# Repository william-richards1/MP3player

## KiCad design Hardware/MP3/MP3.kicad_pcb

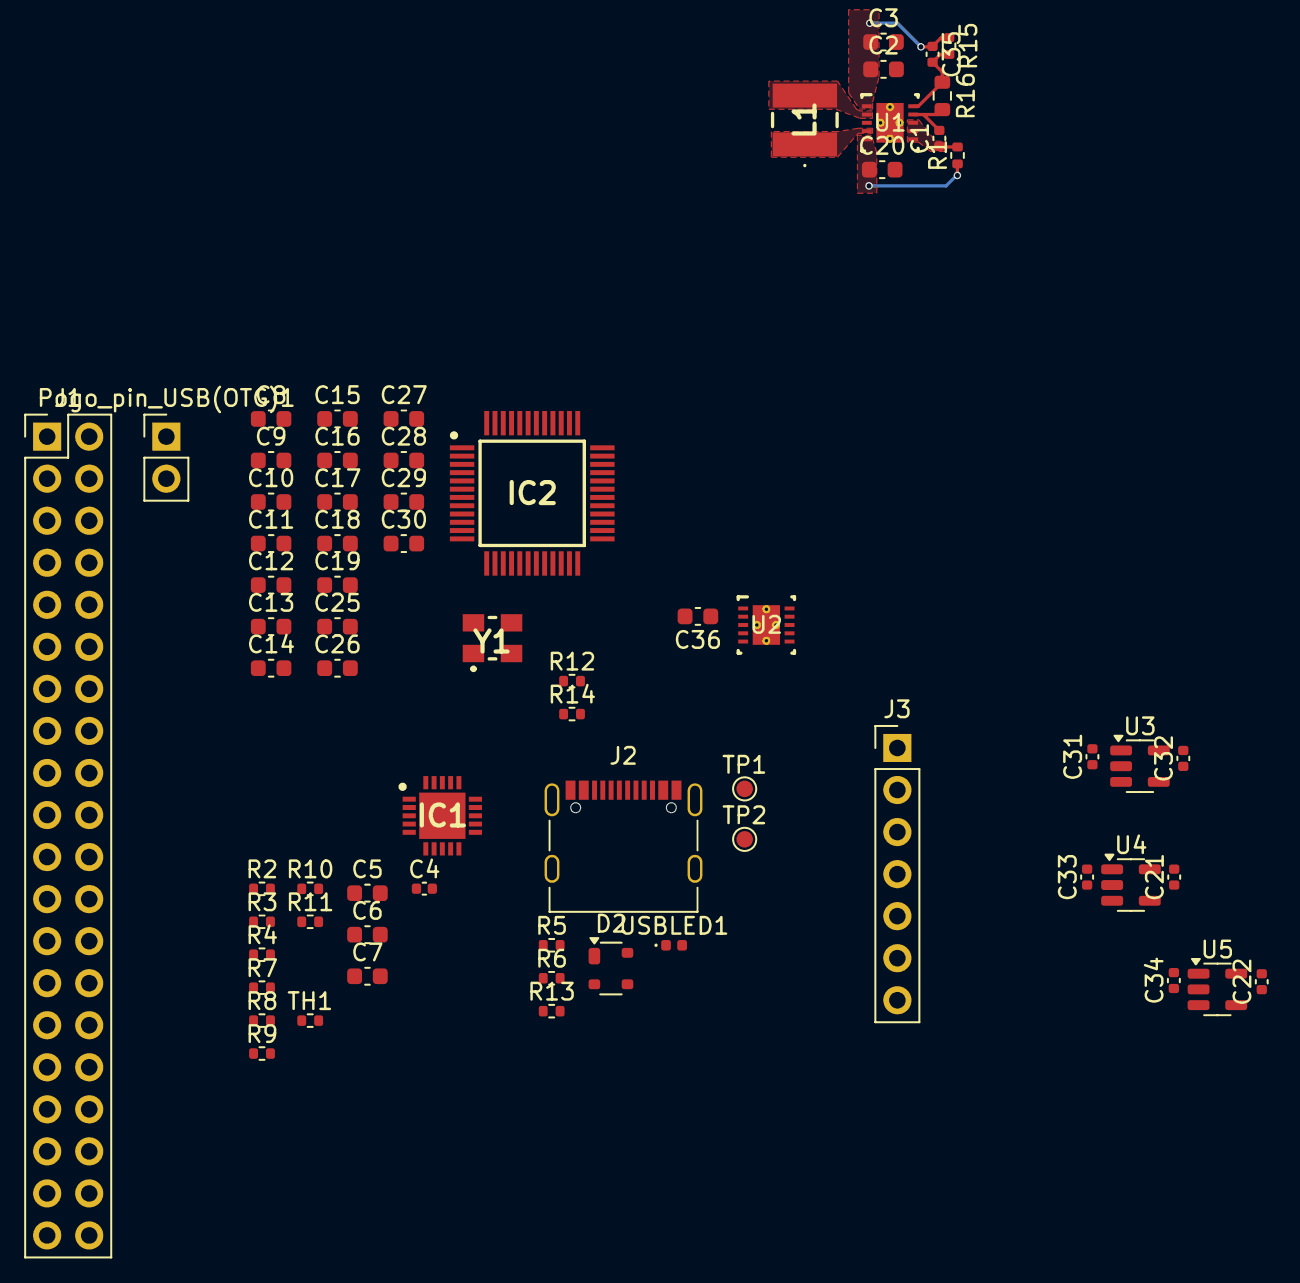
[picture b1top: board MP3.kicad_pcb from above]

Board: 4 copper layers, 68 parts (0 on the bottom side), 38 nets.

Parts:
C1, C4: 0.1uF; C_0402_1005Metric
C2: 22uF; C_0603_1608Metric
C3: 47uF; C_0603_1608Metric
C5, C9, C11, C13, C14, C17, C18, C20, C25, C28, C29, C36: 10uF; C_0603_1608Metric
C6, C7: 4.7uF; C_0603_1608Metric
C8, C10, C12, C15, C19, C26, C30: 0.1uF; C_0603_1608Metric
C16, C27: 470uF; C_0603_1608Metric
C21, C22, C31, C32, C33, C34: 1uF; C_0402_1005Metric
C35: 1nF; C_0402_1005Metric
D2: SP0503BAHT; SOT-143
IC1: MCP73871-2CCI_ML; QFN50P400X400X100-21N-D
IC2: AK4493SEQ; QFP50P900X900X160-48N
J1: Conn_02x20_Odd_Even; PinHeader_2x20_P2.54mm_Vertical
J2: USB_C_Receptacle_USB2.0; USB_C_Receptacle_Palconn_UTC16-G
J3: Conn_01x07_Pin; PinHeader_1x07_P2.54mm_Vertical
L1: LPS4012-223MRC; LPS4012223MRC
Pogo_pin_USB(OTG)1: Conn_01x02_Male; PinHeader_1x02_P2.54mm_Vertical
R1: 100; R_0402_1005Metric
R2: 2.49k; R_0402_1005Metric
R3: 24.9k; R_0402_1005Metric
R4: 2.0k; R_0402_1005Metric
R5, R6, R13: 5.1k; R_0402_1005Metric
R7, R8, R11: 10k; R_0402_1005Metric
R9: 330k; R_0402_1005Metric
R10: 100k; R_0402_1005Metric
R12, R14: 10; R_0402_1005Metric
R15: 1.96MΩ; R_0402_1005Metric
R16: 208kΩ; R_0603_1608Metric
TH1: Thermistor_NTC 10k; R_0402_1005Metric
TP1, TP2: TestPoint; TestPoint_Pad_D1.0mm
U1: TPS63000DRCR; DRC0010J
U2: OPA1622IDRCR; DRC0010J
U3, U5: TPS7A20xxxDBV; SOT-23-5
U4: TPS7A2033PDBVR; SOT-23-5
USBLED1: WHITE_LED; LED_0402_1005Metric
Y1: ABM8-22.5792MHZ-D2Y-T; ABM810000MHZ12D2W

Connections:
3V3: C8.2, C9.1, IC1.4 (PROG2), IC2.48 (TVDD), R7.1, R8.2, R11.1
+5.2V: C2.1, C3.1, C31.2, C33.2, C34.2, C35.1, R15.1, U1.1 (VOUT), U3.1 (IN), U4.1 (IN), U5.1 (IN)
+5V: C22.2, C36.1, U2.2 (V+), U5.5 (OUT)
+A3V3: C10.1, C11.1, C21.2, IC2.44 (AVDD), U4.5 (OUT), Y1.1 (X1)
+A5V: C16.1, C18.1, C19.1, C25.1, C26.1, C27.1, C32.2, IC2.27 (VDDR_1), IC2.28 (VDDR_2), IC2.33 (VDDL_1), IC2.34 (VDDL_2), R12.1, R14.1, U3.5 (OUT)
/3.3v: J1.1, J1.17
/5V: J1.2, J1.4
/DAC+AMP/CLOCK: IC2.46 (MCLK), Y1.3 (X2)
/DAC+AMP/LEFT+: IC2.36 (AOUTLP), U2.1 (INA+)
/DAC+AMP/LEFT-: IC2.35 (AOUTLN), U2.10 (INA-)
/DAC+AMP/RIGHT+: IC2.25 (AOUTRP), U2.5 (INB+)
/DAC+AMP/RIGHT-: IC2.26 (AOUTRN), U2.6 (INB-)
/DAC+AMP/VREFHL: C12.1, C13.1, IC2.41 (VREFHL_1), IC2.42 (VREFHL_2), R12.2
/DAC+AMP/VREFHR: C14.1, C15.1, IC2.19 (VREFHR_1), IC2.20 (VREFHR_2), R14.2
/Data+: D2.4 (K), J2.A6 (D+), J2.B6 (D+), Pogo_pin_USB(OTG)1.1, TP2.1
/Data-: D2.3 (K), J2.A7 (D-), J2.B7 (D-), Pogo_pin_USB(OTG)1.2, TP1.1
/GND: J1.6, J1.9, J1.14, J1.20, J1.25, J1.30, J1.34, J1.39
/Power/CE: IC1.17 (CE), R11.2
/Power/Cell: C7.1, IC1.14 (VBAT_1), IC1.15 (VBAT_2), IC1.16 (VBAT_SENSE)
/Power/FB: C35.2, R15.2, R16.1, U1.10 (FB)
/Power/MCPout: C6.1, C20.1, IC1.1 (OUT_1), IC1.20 (OUT_2), R1.1, U1.5 (VIN)
/Power/PG: IC1.6 (~PG), R7.2
/Power/STAT2: IC1.7 (STAT2), R8.1
GND: C1.2, C2.2, C3.2, C4.1, C5.2, C6.2, C7.2, C8.1, C9.2, C10.2, C11.2, C12.2, C13.2, C14.2, C15.2, C16.2, C17.2, C18.2, C19.2, C20.2, C21.1, C22.1, C25.2, C26.2, C27.2, C28.2, C29.1, C30.1, C31.1, C32.1, C33.1, C34.1, D2.1 (A), IC1.3 (SEL), IC1.9 (~TE), IC1.10 (VSS_1), IC1.11 (VSS_2), IC1.21 (EP), IC2.6 (SSLOW/WCK), IC2.7 (SMUTE/CSN), IC2.12 (DIF2/CAD0), IC2.13 (PSN), IC2.15 (DEM0), IC2.17 (ACKS/CAD1), IC2.18 (TESTE), IC2.21 (VREFLR_1), IC2.22 (VREFLR_2), IC2.24 (NC_1), IC2.29 (VSSR_1), IC2.30 (VSSR_2), IC2.31 (VSSL_1), IC2.32 (VSSL_2), IC2.37 (NC_2), IC2.39 (VREFLL_1), IC2.40 (VREFLL_2), IC2.43 (NC_3), IC2.45 (AVSS), IC2.47 (DVSS), J2.A1 (GND), J2.A12 (GND), J2.B1 (GND), J2.B12 (GND), J2.S1 (SHIELD), R2.1, R3.1, R4.2, R5.2, R6.2, R10.2, R16.2, TH1.2, U1.3 (PGND), U1.9 (GND), U1.11 (PAD), U2.3 (GND), U2.4 (V-), U2.11 (PAD), U3.2 (GND), U4.2 (GND), U5.2 (GND), USBLED1.1 (K), Y1.2 (GND_1), Y1.4 (GND_2)
unnamed: IC1.13 (PROG1), R2.2
unnamed: IC1.12 (PROG3), R3.2
unnamed: IC1.5 (THERM), TH1.1
unnamed: IC1.2 (VPCC), R9.2, R10.1
unnamed: C29.2, C30.2, IC2.1 (DVDD)
unnamed: C17.1, IC2.38 (VCML)
unnamed: C28.1, IC2.23 (VCMR)
unnamed: J2.A5 (CC1), R5.1
unnamed: J2.B5 (CC2), R6.1
unnamed: C1.1, R1.2, U1.6 (EN), U1.7 (PS_SYNC), U1.8 (VINA)
unnamed: L1.1, U1.4 (L1)
unnamed: L1.2, U1.2 (L2)
unnamed: R13.2, USBLED1.2 (A)
VBUS: C4.2, C5.1, D2.2 (K), IC1.18 (IN_1), IC1.19 (IN_2), J2.A4 (VBUS), J2.A9 (VBUS), J2.B4 (VBUS), J2.B9 (VBUS), R9.1, R13.1

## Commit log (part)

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2026-01-28 Schematic notes
    - notes regarding schematic layout and included ICs
2026-02-14 Large symbol import
    - 5V boost
    - Battery charger IC
    - USB behaviour IC
2026-05-17 Large additions, DAC schematic work started
2026-05-17 More changes
2026-06-29 feat: Made some changes to the DAC. Explicitly using register control (using I2C) with PCM audio. Planning to use 5.2V buck on 5V line, then Low noise LDO VREF for DAC, another for AMP power, and a 3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
2026-06-30 feat: Large progress made on the power system. Next steps, find oscillator, sort out LDO footprints, add OLED connectors and encoder connector.
